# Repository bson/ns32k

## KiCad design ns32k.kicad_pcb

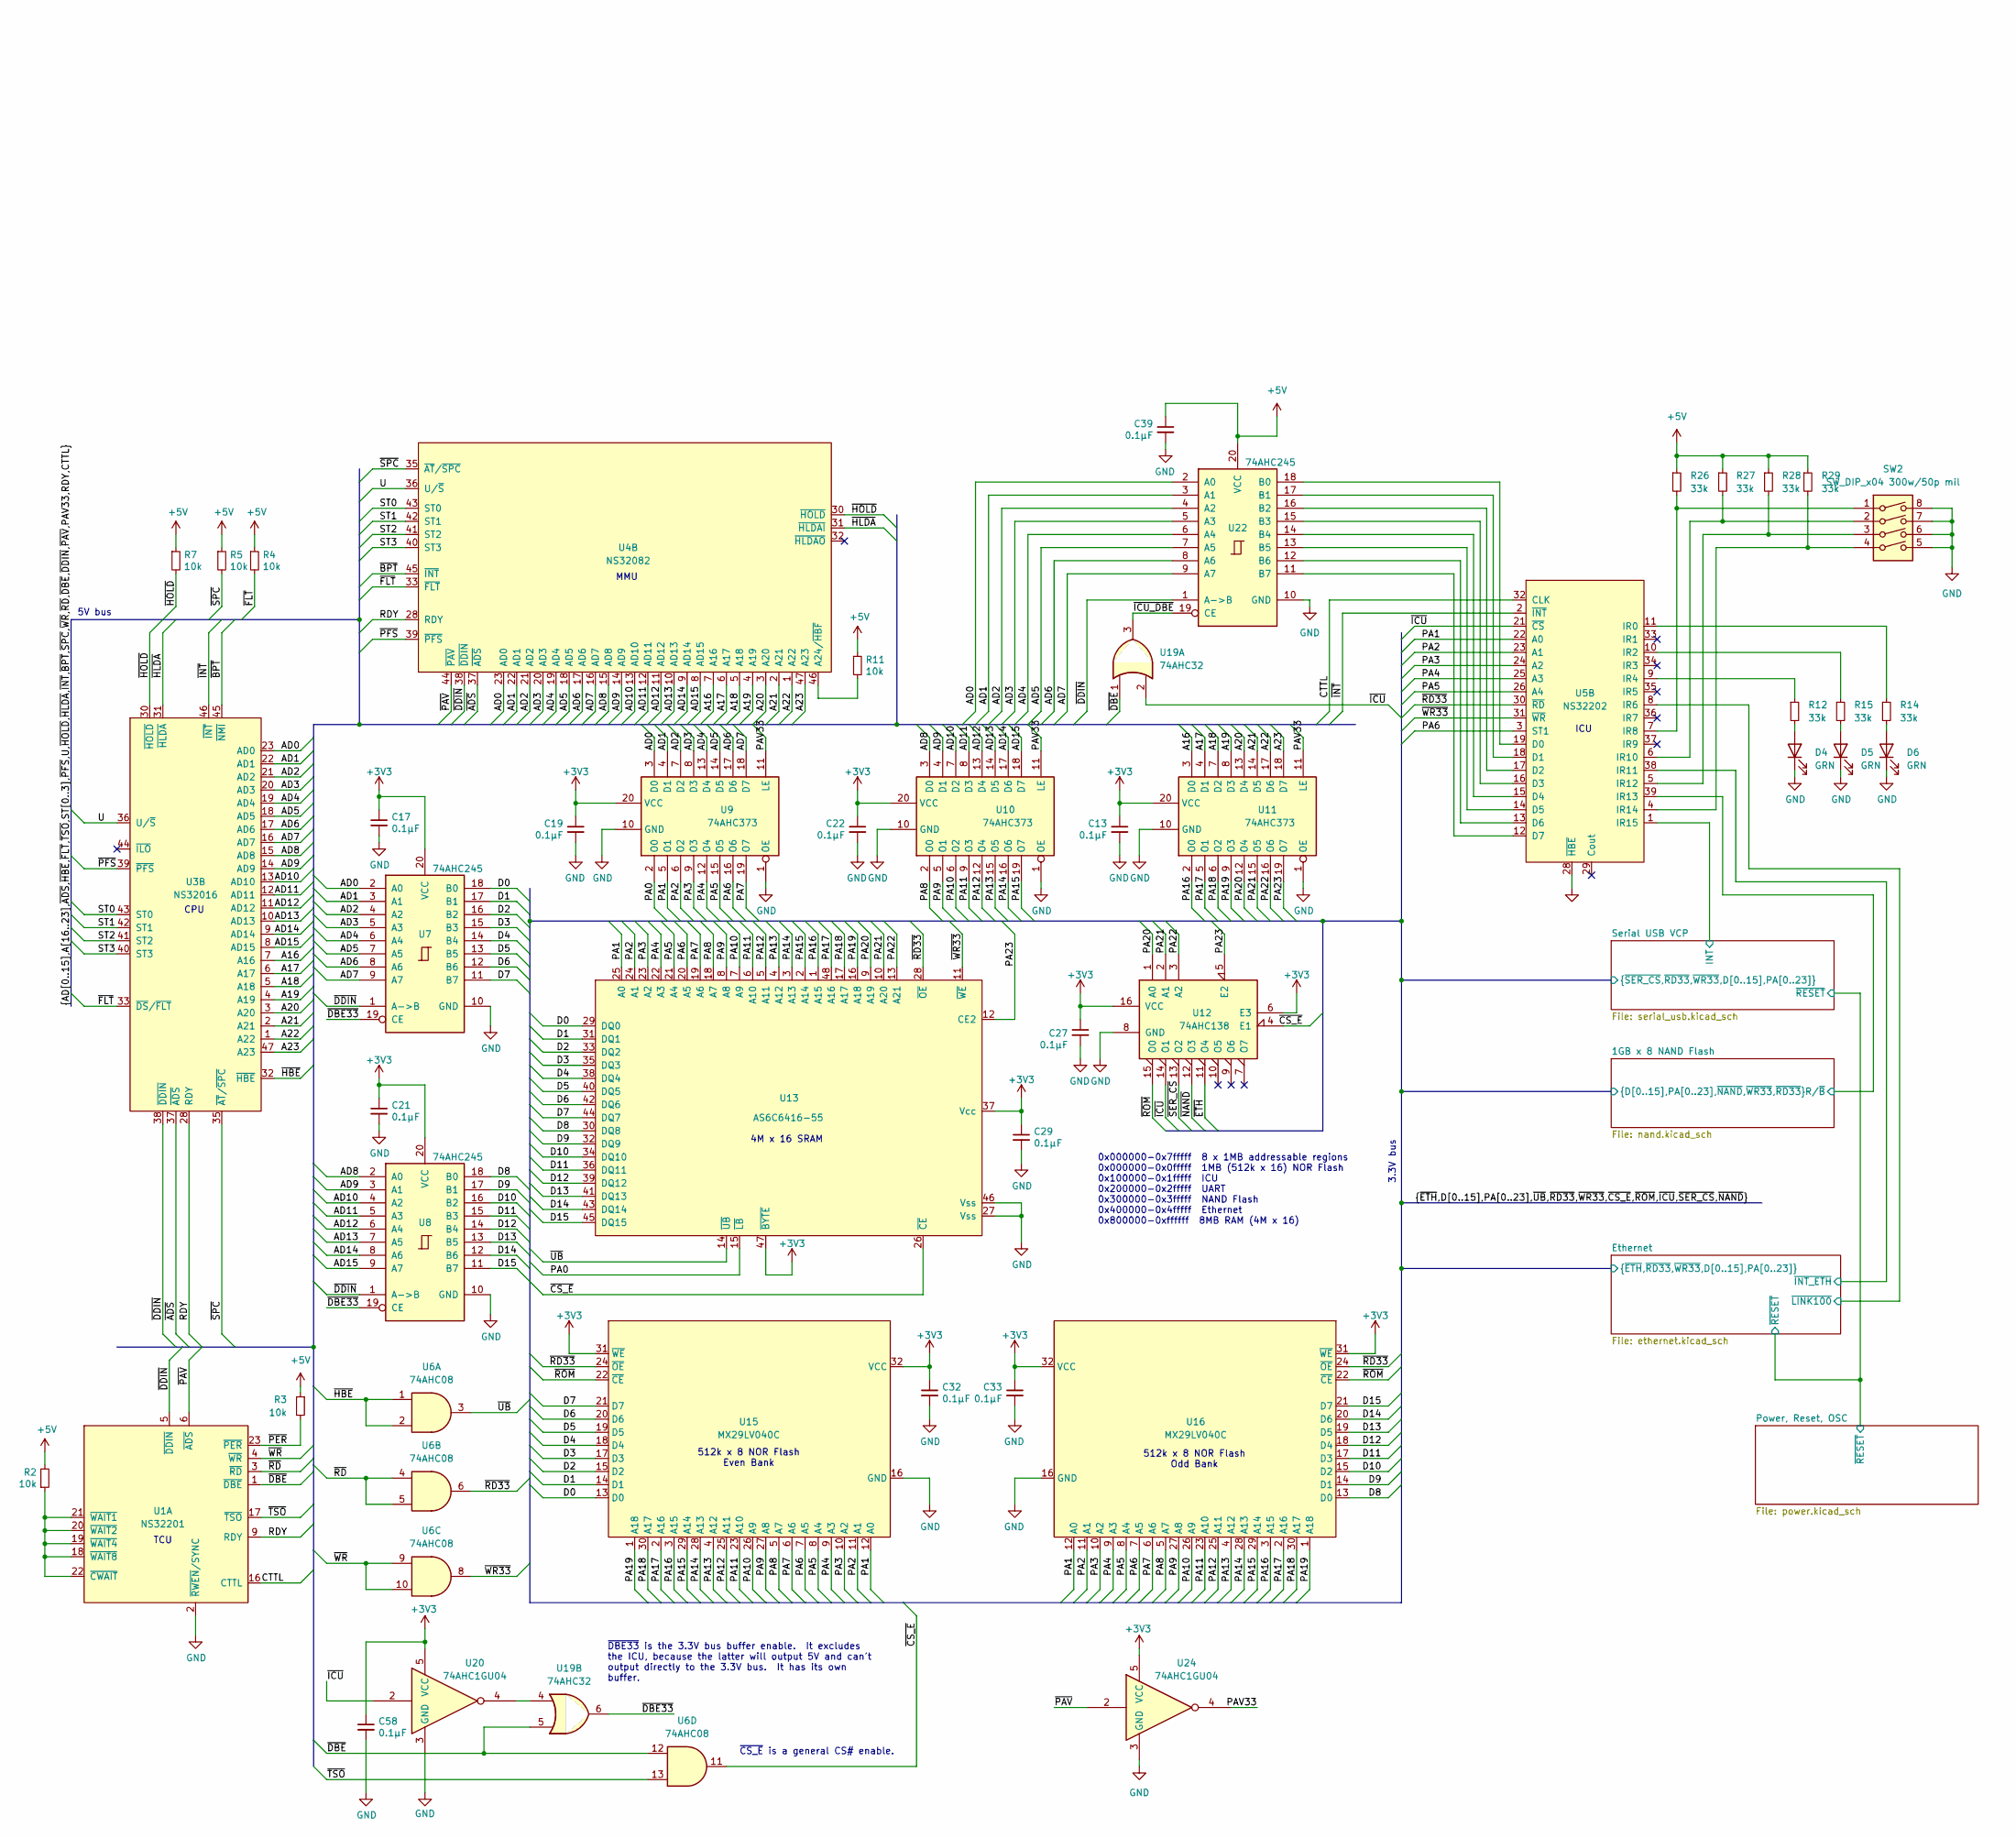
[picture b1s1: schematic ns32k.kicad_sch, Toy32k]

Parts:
C13, C17, C19, C21, C22, C27, C29, C32, C33, C39, C58: 0.1µF; C_0402_1005Metric; LCSC C3012376
D4, D5, D6: GRN; D_0603_1608Metric; LCSC C5246833
R2, R3, R4, R5, R7, R11: 10k; R_0402_1005Metric; LCSC C375970
R12, R14, R15, R26, R27, R28, R29: 33k; R_0402_1005Metric; LCSC C2906928
SW2: SW_DIP_x04 300w/50p mil; SW_DIP_SPSTx04_Slide_Copal_CHS-04B_W7.62mm_P1.27mm; LCSC C18198092
U1: NS32201; DIP-24_W15.24mm_Socket
U3: NS32016; DIP-48_W15.24mm_Socket
U4: NS32082; DIP-48_W15.24mm_Socket
U5: NS32202; DIP-40_W15.24mm_Socket
U6: 74AHC08; TSSOP-14_4.4x5mm_P0.65mm; LCSC C842279
U7, U8, U22: 74AHC245; TSSOP-20_4.4x6.5mm_P0.65mm; LCSC C5516
U9, U10, U11: 74AHC373; TSSOP-20_4.4x6.5mm_P0.65mm; LCSC C80242
U12: 74AHC138; TSSOP-16_4.4x5mm_P0.65mm; LCSC C352950
U13: AS6C6416-55; TSOP-I-48_18.4x12mm_P0.5mm; LCSC C1349200
U15, U16: MX29LV040C; PLCC-32_THT-Socket
U19: 74AHC32; TSSOP-14_4.4x5mm_P0.65mm; LCSC C2868909
U20, U24: 74AHC1GU04; SOT-23-5; LCSC C22384791

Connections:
+3V3: C13.1, C17.1, C19.1, C21.1, C22.1, C27.1, C29.1, C32.1, C33.1, C58.1, U7.20 (VCC), U8.20 (VCC), U9.20 (VCC), U10.20 (VCC), U11.20 (VCC), U12.6 (E3), U12.16 (VCC), U13.37 (Vcc), U13.47 (~BYTE), U15.31 (~WE), U15.32 (VCC), U16.31 (~WE), U16.32 (VCC), U20.5 (VCC), U24.5 (VCC); also elsewhere on the board
+5V: C39.1, R2.2, R3.1, R4.1, R5.1, R7.1, R11.1, R26.1, R27.1, R28.1, R29.1, U22.20 (VCC); also elsewhere on the board
/1GB x 8 NAND Flash/R/~B: U5.39 (IR13); also elsewhere on the board
/A16: U3.7 (A16), U4.7 (A16), U11.3 (D0)
/A17: U3.6 (A17), U4.6 (A17), U11.4 (D1)
/A18: U3.5 (A18), U4.5 (A18), U11.7 (D2)
/A19: U3.4 (A19), U4.4 (A19), U11.8 (D3)
/A20: U3.3 (A20), U4.3 (A20), U11.13 (D4)
/A21: U3.2 (A21), U4.2 (A21), U11.14 (D5)
/A22: U3.1 (A22), U4.1 (A22), U11.17 (D6)
/A23: U3.47 (A23), U4.47 (A23), U11.18 (D7)
/AD0: U3.23 (AD0), U4.23 (AD0), U7.2 (A0), U9.3 (D0), U22.2 (A0)
/AD1: U3.22 (AD1), U4.22 (AD1), U7.3 (A1), U9.4 (D1), U22.3 (A1)
/AD2: U3.21 (AD2), U4.21 (AD2), U7.4 (A2), U9.7 (D2), U22.4 (A2)
/AD3: U3.20 (AD3), U4.20 (AD3), U7.5 (A3), U9.8 (D3), U22.5 (A3)
/AD4: U3.19 (AD4), U4.19 (AD4), U7.6 (A4), U9.13 (D4), U22.6 (A4)
/AD5: U3.18 (AD5), U4.18 (AD5), U7.7 (A5), U9.14 (D5), U22.7 (A5)
/AD6: U3.17 (AD6), U4.17 (AD6), U7.8 (A6), U9.17 (D6), U22.8 (A6)
/AD7: U3.16 (AD7), U4.16 (AD7), U7.9 (A7), U9.18 (D7), U22.9 (A7)
/AD8: U3.15 (AD8), U4.15 (AD8), U8.2 (A0), U10.3 (D0)
/AD9: U3.14 (AD9), U4.14 (AD9), U8.3 (A1), U10.4 (D1)
/AD10: U3.13 (AD10), U4.13 (AD10), U8.4 (A2), U10.7 (D2)
/AD11: U3.12 (AD11), U4.12 (AD11), U8.5 (A3), U10.8 (D3)
/AD12: U3.11 (AD12), U4.11 (AD12), U8.6 (A4), U10.13 (D4)
/AD13: U3.10 (AD13), U4.10 (AD13), U8.7 (A5), U10.14 (D5)
/AD14: U3.9 (AD14), U4.9 (AD14), U8.8 (A6), U10.17 (D6)
/AD15: U3.8 (AD15), U4.8 (AD15), U8.9 (A7), U10.18 (D7)
/CTTL: U1.16 (CTTL), U5.32 (CLK)
/D0: U7.18 (B0), U13.29 (DQ0), U15.13 (D0); also elsewhere on the board
/D1: U7.17 (B1), U13.31 (DQ1), U15.14 (D1); also elsewhere on the board
/D2: U7.16 (B2), U13.33 (DQ2), U15.15 (D2); also elsewhere on the board
/D3: U7.15 (B3), U13.35 (DQ3), U15.17 (D3); also elsewhere on the board
/D4: U7.14 (B4), U13.38 (DQ4), U15.18 (D4); also elsewhere on the board
/D5: U7.13 (B5), U13.40 (DQ5), U15.19 (D5); also elsewhere on the board
/D6: U7.12 (B6), U13.42 (DQ6), U15.20 (D6); also elsewhere on the board
/D7: U7.11 (B7), U13.44 (DQ7), U15.21 (D7); also elsewhere on the board
/D8: U8.18 (B0), U13.30 (DQ8), U16.13 (D0)
/D9: U8.17 (B1), U13.32 (DQ9), U16.14 (D1)
/D10: U8.16 (B2), U13.34 (DQ10), U16.15 (D2)
/D11: U8.15 (B3), U13.36 (DQ11), U16.17 (D3)
/D12: U8.14 (B4), U13.39 (DQ12), U16.18 (D4)
/D13: U8.13 (B5), U13.41 (DQ13), U16.19 (D5)
/D14: U8.12 (B6), U13.43 (DQ14), U16.20 (D6)
/D15: U8.11 (B7), U13.45 (DQ15), U16.21 (D7)
/Ethernet/~INT_ETH: U5.38 (IR11); also elsewhere on the board
/Ethernet/~LINK100: U5.8 (IR6); also elsewhere on the board
/PA0: U9.2 (O0), U13.15 (~LB)
/PA1: U5.22 (A0), U9.5 (O1), U13.25 (A0), U15.12 (A0), U16.12 (A0); also elsewhere on the board
/PA2: U5.23 (A1), U9.6 (O2), U13.24 (A1), U15.11 (A1), U16.11 (A1); also elsewhere on the board
/PA3: U5.24 (A2), U9.9 (O3), U13.23 (A2), U15.10 (A2), U16.10 (A2); also elsewhere on the board
/PA4: U5.25 (A3), U9.12 (O4), U13.22 (A3), U15.9 (A3), U16.9 (A3)
/PA5: U5.26 (A4), U9.15 (O5), U13.21 (A4), U15.8 (A4), U16.8 (A4)
/PA6: U5.3 (ST1), U9.16 (O6), U13.20 (A5), U15.7 (A5), U16.7 (A5)
/PA7: U9.19 (O7), U13.19 (A6), U15.6 (A6), U16.6 (A6)
/PA8: U10.2 (O0), U13.18 (A7), U15.5 (A7), U16.5 (A7)
/PA9: U10.5 (O1), U13.8 (A8), U15.27 (A8), U16.27 (A8)
/PA10: U10.6 (O2), U13.7 (A9), U15.26 (A9), U16.26 (A9)
/PA11: U10.9 (O3), U13.6 (A10), U15.23 (A10), U16.23 (A10)
/PA12: U10.12 (O4), U13.5 (A11), U15.25 (A11), U16.25 (A11)
/PA13: U10.15 (O5), U13.4 (A12), U15.4 (A12), U16.4 (A12)
/PA14: U10.16 (O6), U13.3 (A13), U15.28 (A13), U16.28 (A13)
/PA15: U10.19 (O7), U13.2 (A14), U15.29 (A14), U16.29 (A14)
/PA16: U11.2 (O0), U13.1 (A15), U15.3 (A15), U16.3 (A15)
/PA17: U11.5 (O1), U13.48 (A16), U15.2 (A16), U16.2 (A16)
/PA18: U11.6 (O2), U13.17 (A17), U15.30 (A17), U16.30 (A17)
/PA19: U11.9 (O3), U13.16 (A18), U15.1 (A18), U16.1 (A18)
/PA20: U11.12 (O4), U12.1 (A0), U13.9 (A19)
/PA21: U11.15 (O5), U12.2 (A1), U13.10 (A20)
/PA22: U11.16 (O6), U12.3 (A2), U13.13 (A21)
/PA23: U11.19 (O7), U12.5 (E2), U13.12 (CE2)
/PAV33: U9.11 (LE), U10.11 (LE), U11.11 (LE), U24.4
/RDY: U1.9 (RDY), U3.28 (RDY), U4.28 (RDY)
/ST0: U3.43 (ST0), U4.43 (ST0)
/ST1: U3.42 (ST1), U4.42 (ST1)
/ST2: U3.41 (ST2), U4.41 (ST2)
/ST3: U3.40 (ST3), U4.40 (ST3)
/Serial USB VCP/INT: U5.1 (IR15); also elsewhere on the board
/U: U3.36 (U/~S), U4.36 (U/~S)
/~ADS: U3.37 (~ADS), U4.37 (~ADS)
/~BPT: U3.45 (~NMI), U4.45 (~INT)
/~CS_E: U6.11, U12.4 (E1), U13.26 (~CE)
/~DBE33: U7.19 (CE), U8.19 (CE), U19.6
/~DBE: U1.1 (~DBE), U6.12, U19.1, U19.5
/~DDIN: U1.5 (~DDIN), U3.38 (~DDIN), U4.38 (~DDIN), U7.1 (A->B), U8.1 (A->B), U22.1 (A->B)
/~ETH: U12.11 (O4); also elsewhere on the board
/~FLT: R4.2, U3.33 (~DS/~FLT), U4.33 (~FLT)
/~HBE: U3.32 (~HBE), U6.1, U6.2
/~HLDA: U3.31 (~HLDA), U4.31 (~HLDAI)
/~HOLD: R7.2, U3.30 (~HOLD), U4.30 (~HOLD)
/~ICU_DBE: U19.3, U22.19 (CE)
/~ICU: U5.21 (~CS), U12.14 (O1), U19.2, U20.2
/~INT: U3.46 (~INT), U5.2 (~INT)
/~NAND: U12.12 (O3); also elsewhere on the board
/~PAV: U1.6 (~ADS), U4.44 (~PAV), U24.2
/~PER: R3.2, U1.23 (~PER)
/~PFS: U3.39 (~PFS), U4.39 (~PFS)
/~RD33: U5.30 (~RD), U6.6, U13.28 (~OE), U15.24 (~OE), U16.24 (~OE); also elsewhere on the board
/~RD: U1.3 (~RD), U6.4, U6.5
/~ROM: U12.15 (O0), U15.22 (~CE), U16.22 (~CE)
/~SER_CS: U12.13 (O2); also elsewhere on the board
/~SPC: R5.2, U3.35 (~AT/~SPC), U4.35 (~AT/~SPC)
/~TSO: U1.17 (~TSO), U6.13
/~UB: U6.3, U13.14 (~UB)
/~WR33: U5.31 (~WR), U6.8, U13.11 (~WE); also elsewhere on the board
/~WR: U1.4 (~WR), U6.9, U6.10
GND: C13.2, C17.2, C19.2, C21.2, C22.2, C27.2, C29.2, C32.2, C33.2, C39.2, C58.2, D4.1 (K), D5.1 (K), D6.1 (K), SW2.5, SW2.6, SW2.7, SW2.8, U1.2 (~RWEN/SYNC), U5.28 (~HBE), U7.10 (GND), U8.10 (GND), U9.1 (OE), U9.10 (GND), U10.1 (OE), U10.10 (GND), U11.1 (OE), U11.10 (GND), U12.8 (GND), U13.27 (Vss), U13.46 (Vss), U15.16 (GND), U16.16 (GND), U20.3 (GND), U22.10 (GND), U24.3 (GND); also elsewhere on the board
unnamed: D4.2 (A), R12.2
unnamed: D5.2 (A), R15.2
unnamed: D6.2 (A), R14.2
unnamed: R2.1, U1.18 (~WAIT8), U1.19 (~WAIT4), U1.20 (~WAIT2), U1.21 (~WAIT1), U1.22 (~CWAIT)
unnamed: R11.2, U4.46 (A24/~HBF)
unnamed: R14.1, U5.11 (IR0)
unnamed: R15.1, U5.10 (IR2)
unnamed: R12.1, U5.9 (IR4)
unnamed: R26.2, SW2.1, U5.7 (IR8)
unnamed: R27.2, SW2.2, U5.6 (IR10)
unnamed: R28.2, SW2.3, U5.5 (IR12)
unnamed: R29.2, SW2.4, U5.4 (IR14)
unnamed: U19.4, U20.4
unnamed: U5.19 (D0), U22.18 (B0)
unnamed: U5.18 (D1), U22.17 (B1)
unnamed: U5.17 (D2), U22.16 (B2)
unnamed: U5.16 (D3), U22.15 (B3)
unnamed: U5.15 (D4), U22.14 (B4)
unnamed: U5.14 (D5), U22.13 (B5)
unnamed: U5.13 (D6), U22.12 (B6)
unnamed: U5.12 (D7), U22.11 (B7)

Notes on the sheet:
~{CS_E} is a general CS# enable.
0x000000-0x7fffff 8 x 1MB addressable regions 0x000000-0x0fffff 1MB (512k x 16) NOR Flash 0x100000-0x1fffff ICU 0x200000-0x2fffff UART 0x300000-0x3fffff NAND Flash 0x400000-0x4fffff Ethernet 0x800000-0xffffff 8MB RAM (4M x 16)
MMU
CPU
5V bus
512k x 8 NOR Flash Odd Bank
4M x 16 SRAM
~{DBE33} is the 3.3V bus buffer enable. It excludes the ICU, because the latter will output 5V and can't output directly to the 3.3V bus. It has its own buffer.
ICU
3.3V bus
TCU
512k x 8 NOR Flash Even Bank

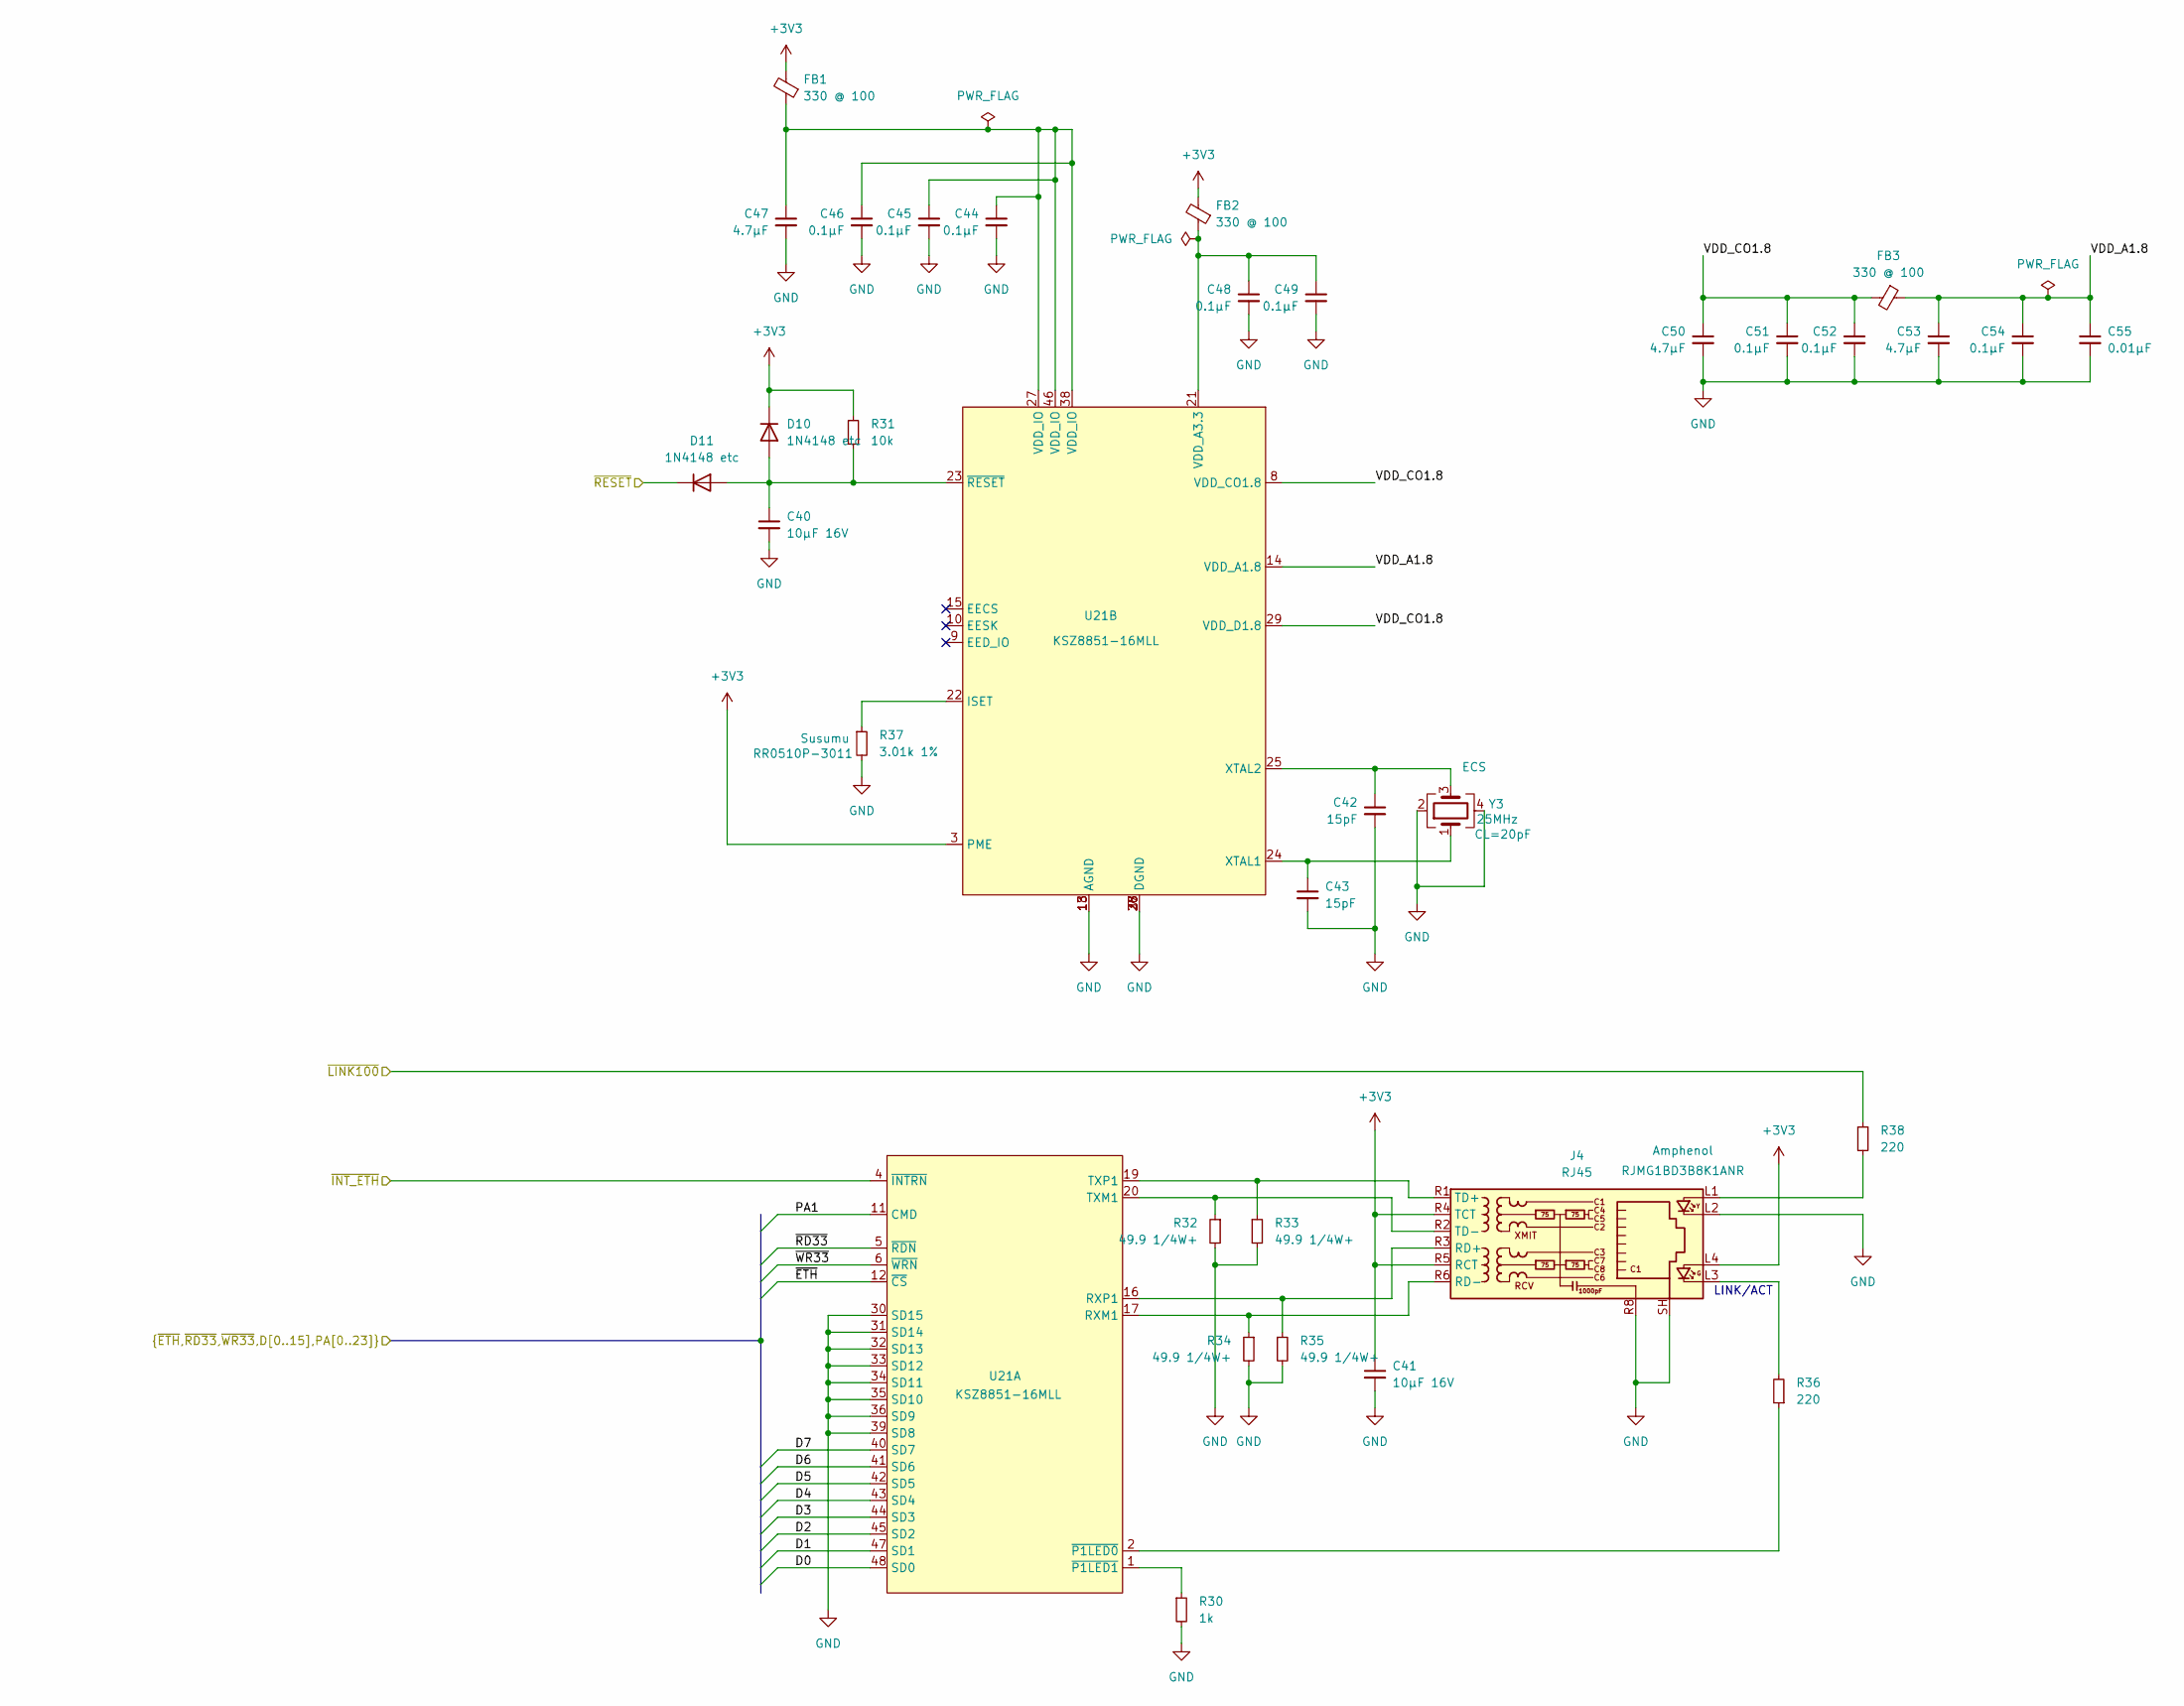
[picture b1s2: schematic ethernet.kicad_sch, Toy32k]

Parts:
C40, C41: 10µF 16V; C_0603_1608Metric; LCSC C109457
C42, C43: 15pF; C_0402_1005Metric; LCSC C1852854
C44, C45, C46, C48, C49, C51, C52, C54: 0.1µF; C_0402_1005Metric; LCSC C3012376
C47, C50, C53: 4.7µF; C_0805_2012Metric; LCSC C84718
C55: 0.01µF; C_0402_1005Metric; LCSC C327025
D10, D11: 1N4148 etc; D_0603_1608Metric; LCSC C2902912
FB1, FB2, FB3: 330 @ 100; L_0402_1005Metric; LCSC C108308
J4: RJ45; RJ45_Amphenol_RJMG1BD3B8K1ANR; Part RJMG1BD3B8K1ANR
R30: 1k; R_0402_1005Metric; LCSC C139047
R31: 10k; R_0402_1005Metric; LCSC C375970
R32, R33, R34, R35: 49.9 1/4W+; R_0805_2012Metric; LCSC C4088942
R36, R38: 220; R_0402_1005Metric; LCSC C453594
R37: 3.01k 1%; R_0402_1005Metric; Part RR0510P-3011; LCSC C25889
U21: KSZ8851-16MLL; LQFP-48_7x7mm_P0.5mm; LCSC C633713
Y3: 25MHz; Crystal_SMD_3225-4Pin_3.2x2.5mm; LCSC C7294571

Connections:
+3V3: C41.1, D10.1 (K), FB1.2, FB2.2, J4.L4, J4.R4 (TCT), J4.R5 (RCT), R31.1, U21.3 (PME); also elsewhere on the board
/D0: U21.48 (SD0); also elsewhere on the board
/D1: U21.47 (SD1); also elsewhere on the board
/D2: U21.45 (SD2); also elsewhere on the board
/D3: U21.44 (SD3); also elsewhere on the board
/D4: U21.43 (SD4); also elsewhere on the board
/D5: U21.42 (SD5); also elsewhere on the board
/D6: U21.41 (SD6); also elsewhere on the board
/D7: U21.40 (SD7); also elsewhere on the board
/Ethernet/VDD_A1.8: C53.1, C54.1, C55.1, FB3.1, U21.14 (VDD_A1.8)
/Ethernet/VDD_CO1.8: C50.1, C51.1, C52.1, FB3.2, U21.8 (VDD_CO1.8), U21.29 (VDD_D1.8)
/Ethernet/~INT_ETH: U21.4 (~INTRN); also elsewhere on the board
/Ethernet/~LINK100: R38.1; also elsewhere on the board
/Ethernet/~RESET: D11.1 (K); also elsewhere on the board
/PA1: U21.11 (CMD); also elsewhere on the board
/~ETH: U21.12 (~CS); also elsewhere on the board
/~RD33: U21.5 (~RDN); also elsewhere on the board
/~WR33: U21.6 (~WRN); also elsewhere on the board
GND: C40.2, C41.2, C42.2, C43.2, C44.2, C45.2, C46.2, C47.2, C48.2, C49.2, C50.2, C51.2, C52.2, C53.2, C54.2, C55.2, J4.L2, J4.R8, J4.SH, R30.2, R32.2, R33.2, R34.2, R35.2, R37.2, U21.7 (DGND), U21.13 (AGND), U21.18 (AGND), U21.26 (DGND), U21.28 (DGND), U21.30 (SD15), U21.31 (SD14), U21.32 (SD13), U21.33 (SD12), U21.34 (SD11), U21.35 (SD10), U21.36 (SD9), U21.37 (DGND), U21.39 (SD8), Y3.2, Y3.4; also elsewhere on the board
unnamed: C44.1, C45.1, C46.1, C47.1, FB1.1, U21.27 (VDD_IO), U21.38 (VDD_IO), U21.46 (VDD_IO)
unnamed: C40.1, D10.2 (A), D11.2 (A), R31.2, U21.23 (~RESET)
unnamed: J4.L1, R38.2
unnamed: J4.L3, R36.2
unnamed: J4.R3 (RD+), R35.1, U21.16 (RXP1)
unnamed: J4.R6 (RD-), R34.1, U21.17 (RXM1)
unnamed: J4.R1 (TD+), R33.1, U21.19 (TXP1)
unnamed: J4.R2 (TD-), R32.1, U21.20 (TXM1)
unnamed: R36.1, U21.2 (~P1LED0)
unnamed: R30.1, U21.1 (~P1LED1)
unnamed: R37.1, U21.22 (ISET)
unnamed: C48.1, C49.1, FB2.1, U21.21 (VDD_A3.3)
unnamed: C43.1, U21.24 (XTAL1), Y3.1
unnamed: C42.1, U21.25 (XTAL2), Y3.3

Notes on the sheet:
LINK/ACT

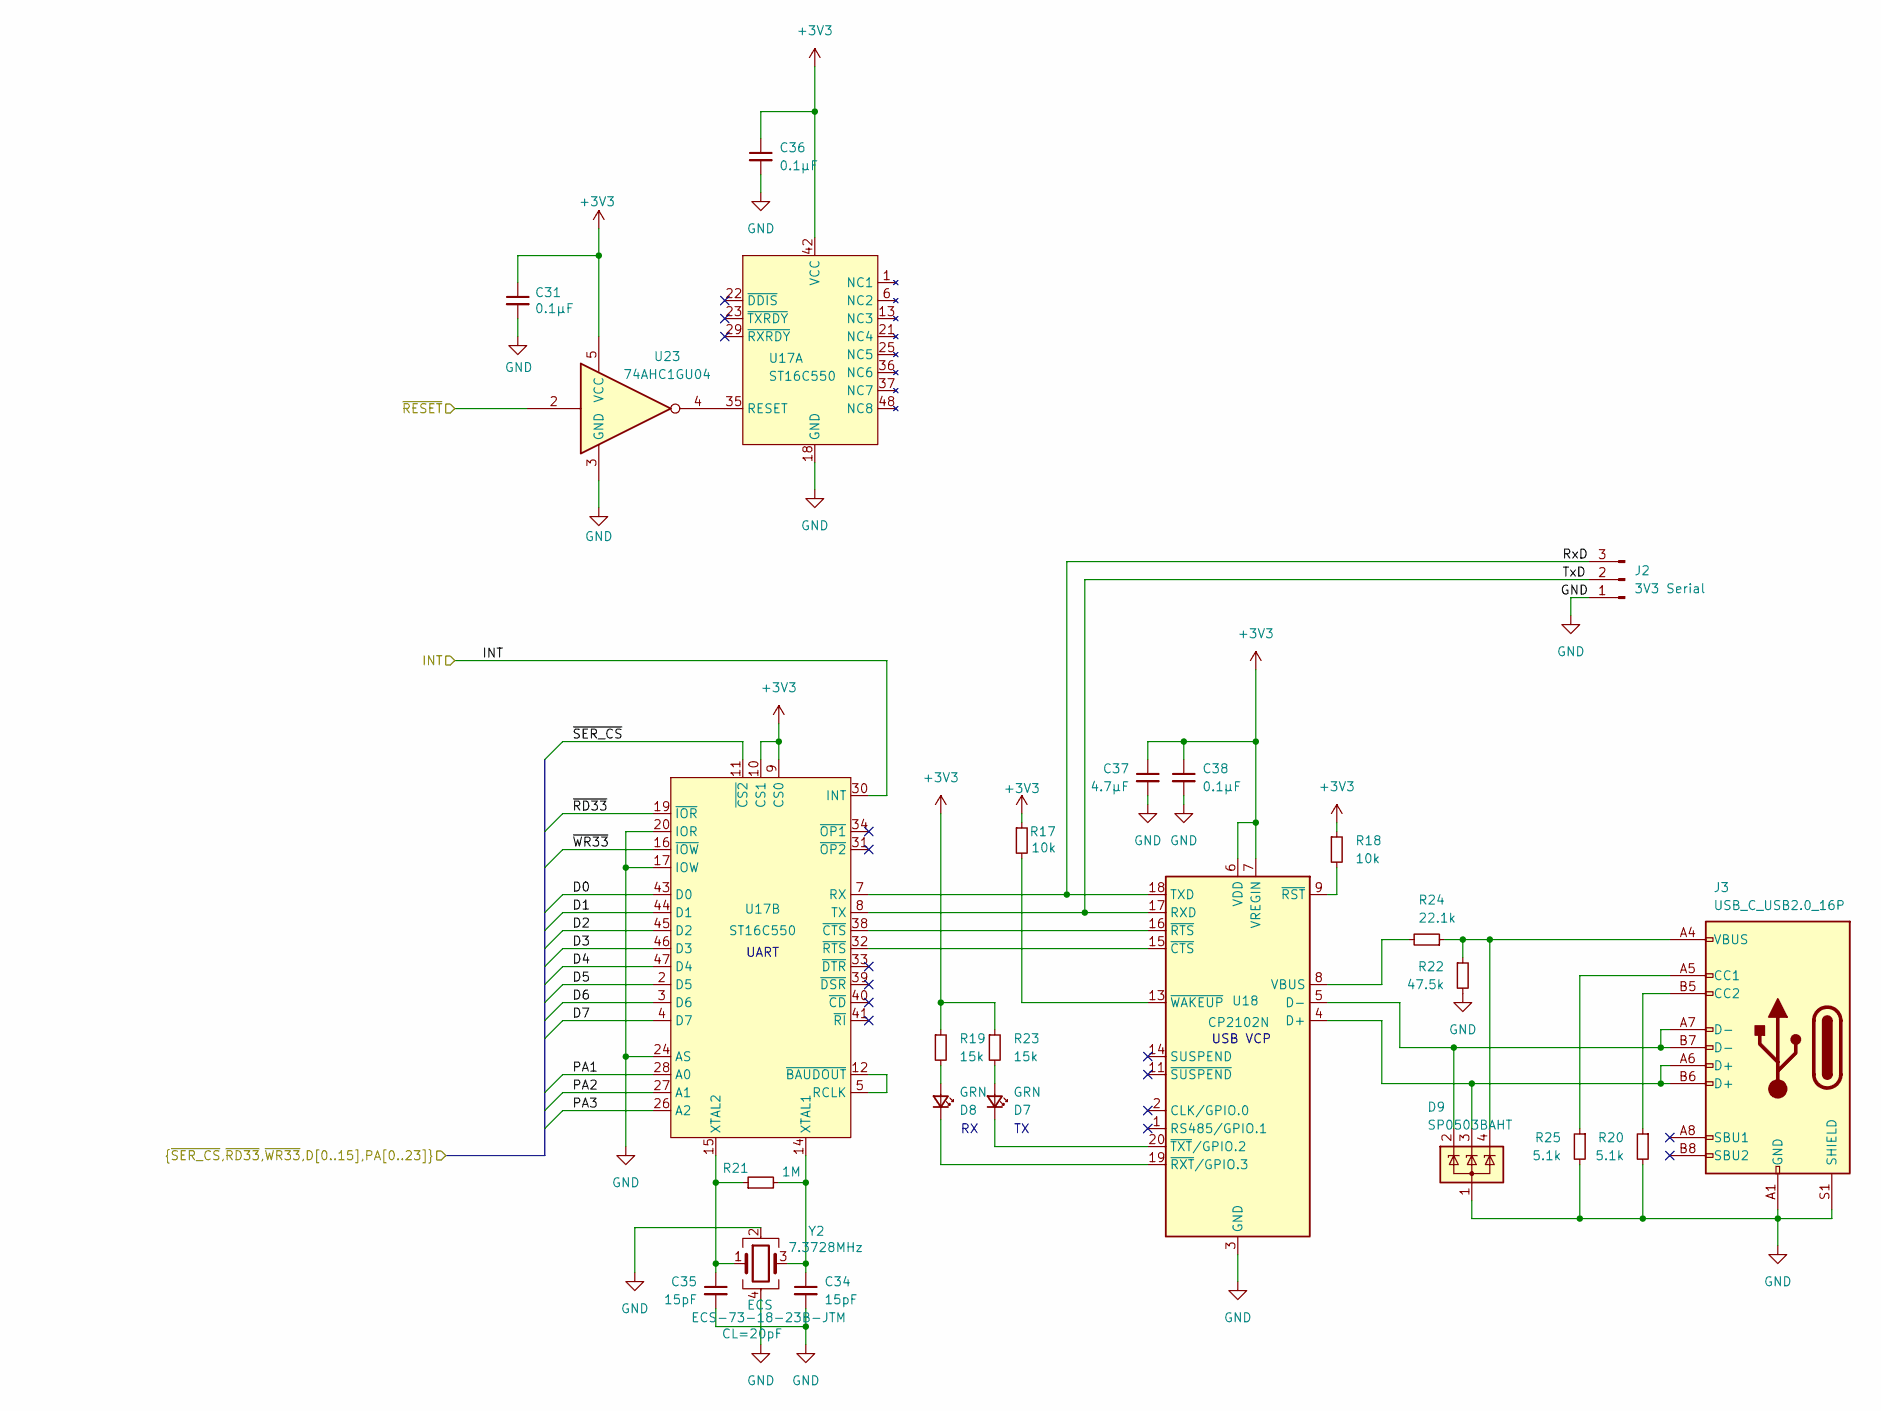
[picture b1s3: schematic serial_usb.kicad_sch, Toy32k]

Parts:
C31, C36, C38: 0.1µF; C_0402_1005Metric; LCSC C3012376
C34, C35: 15pF; C_0402_1005Metric; LCSC C1852854
C37: 4.7µF; C_0805_2012Metric; LCSC C84718
D7, D8: GRN; D_0603_1608Metric; LCSC C5246833
D9: SP0503BAHT; SOT-143; LCSC C5337181
J2: 3V3 Serial; PinHeader_1x03_P2.54mm_Vertical
J3: USB_C_USB2.0_16P; USB_C_Receptacle_HCTL_HC-TYPE-C-16P-01A; LCSC C2909599
R17, R18: 10k; R_0402_1005Metric; LCSC C375970
R19, R23: 15k; R_0402_1005Metric; LCSC C850820
R20, R25: 5.1k; R_0402_1005Metric; LCSC C384321
R21: 1M; R_0402_1005Metric; LCSC C4334825
R22: 47.5k; R_0402_1005Metric; LCSC C3015870
R24: 22.1k; R_0402_1005Metric; LCSC C2929993
U17: ST16C550; TQFP-48_7x7mm_P0.5mm; LCSC C2653190
U18: CP2102N; CP2102N-QFN20; LCSC C969913
U23: 74AHC1GU04; SOT-23-5; LCSC C22384791
Y2: 7.3728MHz; Crystal_SMD_0603-4Pin_6.0x3.5mm; Part ECS-73-18-23B-JTM

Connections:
+3V3: C31.1, C36.1, C37.1, C38.1, R17.1, R18.1, R19.1, R23.1, U17.9 (CS0), U17.10 (CS1), U17.42 (VCC), U18.6 (VDD), U18.7 (VREGIN), U23.5 (VCC); also elsewhere on the board
/D0: U17.43 (D0); also elsewhere on the board
/D1: U17.44 (D1); also elsewhere on the board
/D2: U17.45 (D2); also elsewhere on the board
/D3: U17.46 (D3); also elsewhere on the board
/D4: U17.47 (D4); also elsewhere on the board
/D5: U17.2 (D5); also elsewhere on the board
/D6: U17.3 (D6); also elsewhere on the board
/D7: U17.4 (D7); also elsewhere on the board
/Ethernet/~RESET: U23.2; also elsewhere on the board
/PA1: U17.28 (A0); also elsewhere on the board
/PA2: U17.27 (A1); also elsewhere on the board
/PA3: U17.26 (A2); also elsewhere on the board
/Serial USB VCP/INT: U17.30 (INT); also elsewhere on the board
/Serial USB VCP/RxD: J2.3, U17.7 (RX), U18.18 (TXD)
/Serial USB VCP/TxD: J2.2, U17.8 (TX), U18.17 (RXD)
/~RD33: U17.19 (~IOR); also elsewhere on the board
/~SER_CS: U17.11 (~CS2); also elsewhere on the board
/~WR33: U17.16 (~IOW); also elsewhere on the board
GND: C31.2, C34.2, C35.2, C36.2, C37.2, C38.2, D9.1 (A), J2.1, J3.A1 (GND), J3.A12 (GND), J3.B1 (GND), J3.B12 (GND), J3.S1 (SHIELD), R20.2, R22.2, R25.2, U17.17 (IOW), U17.18 (GND), U17.20 (IOR), U17.24 (AS), U18.3 (GND), U18.12 (GND), U23.3 (GND), Y2.2, Y2.4; also elsewhere on the board
unnamed: D7.2 (A), R23.2
unnamed: D7.1 (K), U18.20 (~TXT/GPIO.2)
unnamed: D8.2 (A), R19.2
unnamed: D8.1 (K), U18.19 (~RXT/GPIO.3)
unnamed: D9.4 (K), J3.A4 (VBUS), J3.A9 (VBUS), J3.B4 (VBUS), J3.B9 (VBUS), R22.1, R24.1
unnamed: J3.A5 (CC1), R25.1
unnamed: J3.B5 (CC2), R20.1
unnamed: U17.35 (RESET), U23.4
unnamed: U17.5 (RCLK), U17.12 (~BAUDOUT)
unnamed: C34.1, R21.2, U17.14 (XTAL1), Y2.3
unnamed: C35.1, R21.1, U17.15 (XTAL2), Y2.1
unnamed: U17.38 (~CTS), U18.16 (~RTS)
unnamed: U17.32 (~RTS), U18.15 (~CTS)
unnamed: D9.3 (K), J3.A6 (D+), J3.B6 (D+), U18.4 (D+)
unnamed: D9.2 (K), J3.A7 (D-), J3.B7 (D-), U18.5 (D-)
unnamed: R24.2, U18.8 (VBUS)
unnamed: R18.2, U18.9 (~RST)
unnamed: R17.2, U18.13 (~WAKEUP)

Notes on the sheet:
USB VCP
UART

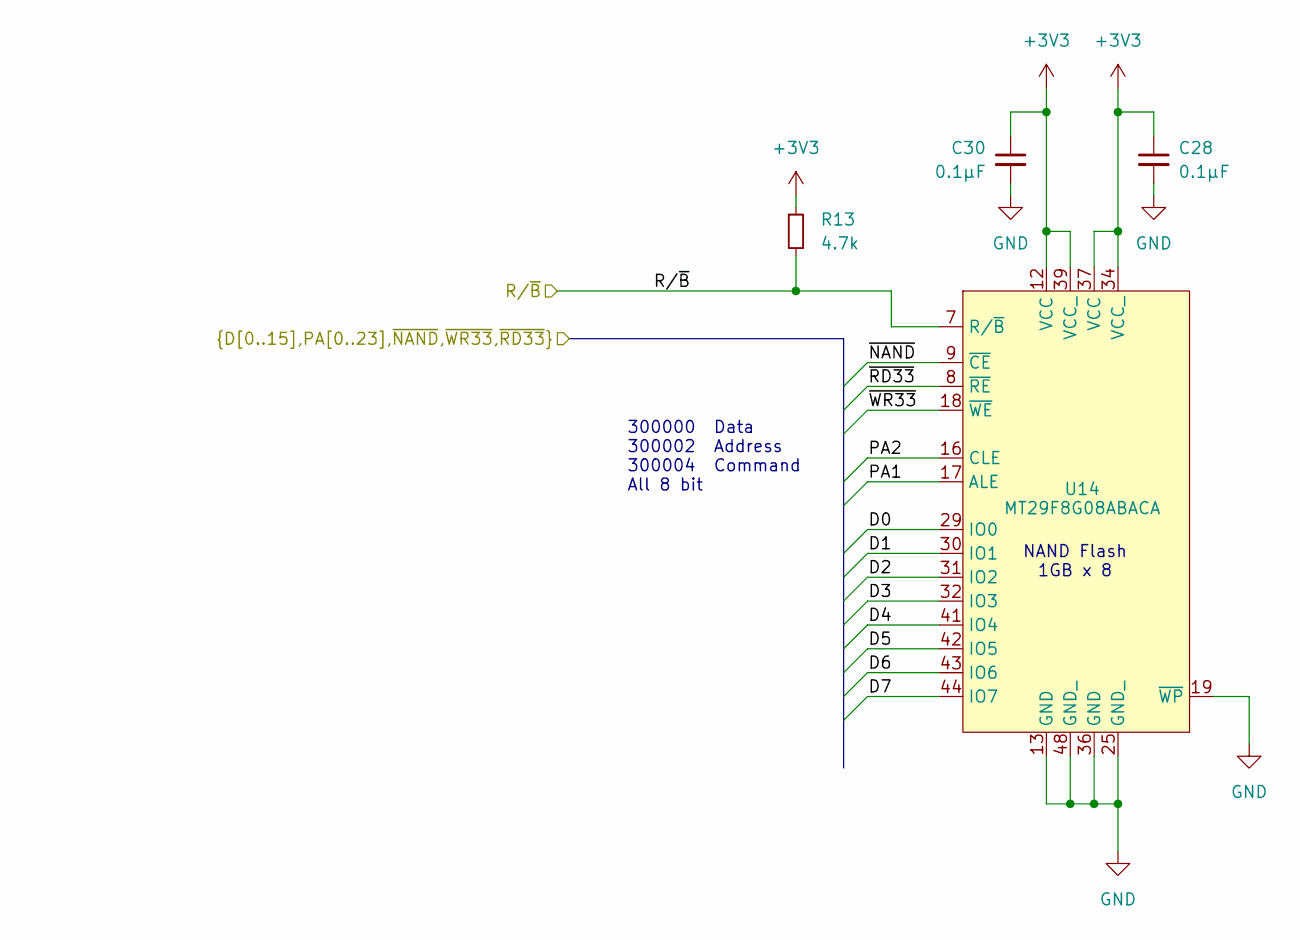
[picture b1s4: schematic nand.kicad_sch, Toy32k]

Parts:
C28, C30: 0.1µF; C_0402_1005Metric; LCSC C3012376
R13: 4.7k; R_0402_1005Metric; LCSC C25940
U14: MT29F8G08ABACA; TSOP-I-48_18.4x12mm_P0.5mm; LCSC C400999

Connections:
+3V3: C28.1, C30.1, R13.1, U14.12 (VCC), U14.34 (VCC_), U14.37 (VCC), U14.39 (VCC_); also elsewhere on the board
/1GB x 8 NAND Flash/R/~B: R13.2, U14.7 (R/~B); also elsewhere on the board
/D0: U14.29 (IO0); also elsewhere on the board
/D1: U14.30 (IO1); also elsewhere on the board
/D2: U14.31 (IO2); also elsewhere on the board
/D3: U14.32 (IO3); also elsewhere on the board
/D4: U14.41 (IO4); also elsewhere on the board
/D5: U14.42 (IO5); also elsewhere on the board
/D6: U14.43 (IO6); also elsewhere on the board
/D7: U14.44 (IO7); also elsewhere on the board
/PA1: U14.17 (ALE); also elsewhere on the board
/PA2: U14.16 (CLE); also elsewhere on the board
/~NAND: U14.9 (~CE); also elsewhere on the board
/~RD33: U14.8 (~RE); also elsewhere on the board
/~WR33: U14.18 (~WE); also elsewhere on the board
GND: C28.2, C30.2, U14.13 (GND), U14.19 (~WP), U14.25 (GND_), U14.36 (GND), U14.48 (GND_); also elsewhere on the board

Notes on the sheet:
NAND Flash 1GB x 8
300000 Data 300002 Address 300004 Command All 8 bit
